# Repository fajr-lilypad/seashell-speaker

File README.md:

# Seashell Speaker!

A bluetooth speaker that automatically plays when tilted, encased in a seashell case!

I came up with this idea when I was thinking about how to expand my audio projects. This was created for hackclub's fallout program, and after first creating an mp3 player, I though the next step would be to make something that could use bluetooth, and then I took it to the next level by making it tilt activated! By coincidence, this is my second ocean-related project, lol. The design was inspired by the story we all know about hearing the ocean come from a shell, and partly inspired by the purple magic conch shell from spongebob, lol.

# Cad Screenshots

<table>
   <tr>
      <td>
   
</td>
      <td>
   
      </td>
   </tr>
</table>

<table>
  <tr>
    <td>
    
    </td>
    <td>
    
    </td>
    <td>
      
    </td>
  </tr>
</table>

Cad Notes:
- Okay, so CAD took a WHILE. Creating such an organic shape was difficult, so ended up relying on the revolve, sweep, and coil tools. Since there arent any tutorials online for creating this type of shell in Fusion either, I had to experiment with blender along with borrowing pieces of 3d models online. Once I had a shape i was happy with, I turned it into a case by splitting it in half, adding holes for magnets, and enclosure for the speaker standoffs for the pcb, and holes for the speaker wires.
- The case itself is pretty easy to use, and I'm happy with how it turned out. If I could go back and change anything, I'd definetly check before hand that my case and pcb were compatible. Orginally, I had planned to tuck my pcb away in the lip/opening of the shell. However, that would be pretty mush impossible without making a HUGE shell case, so I had to basically do a whole redesign of the pcb and case.

# PCB Screenshots

<table>
  <tr>
    <td>
    
    </td>
    <td>
    
    </td>
    <td>
      
    </td>
  </tr>
</table>

  PCB Notes:
   - For the PCB, I did have to go thorugh a few versions. I mostly focused on creating super compact board without hindering the esp32's antenna, which wasn't too bad. However, my first designs were too big too fit in the case, so I had to go back to the drawing board, where I decided to make a round pcb that would sit between the top and bottom halves of the shell.
   - This pcb includes a tilt sensor, charging module, switch, esp32, speaker output headers, and more (see bom)

# Schematic Screenshot

 # Zine !!

 # BOM

 | Item                 | Purpose                       | #        | Cost   | Supplier           | Link                                                                                                                                                                                                                                                                                                                                                                                                                                                                                                                                                                                                                                                                                                                                                                                                                                                                                                                                       |
|----------------------|-------------------------------|----------|--------|--------------------|--------------------------------------------------------------------------------------------------------------------------------------------------------------------------------------------------------------------------------------------------------------------------------------------------------------------------------------------------------------------------------------------------------------------------------------------------------------------------------------------------------------------------------------------------------------------------------------------------------------------------------------------------------------------------------------------------------------------------------------------------------------------------------------------------------------------------------------------------------------------------------------------------------------------------------------------|
| SW-520D              | Sensor                        | 1        | $1.13  | Aliexpress         | https://www.aliexpress.us/item/3256805875302445.html?spm=a2g0o.productlist.main.8.2a455a92Y7JwEt&aem_p4p_detail=202606091117086506985475300170000304694&algo_pvid=fe4f2528-e777-4706-bdc4-faf0cd102a94&algo_exp_id=fe4f2528-e777-4706-bdc4-faf0cd102a94-7&pdp_ext_f=%7B%22order%22%3A%22408%22%2C%22eval%22%3A%221%22%2C%22fromPage%22%3A%22search%22%7D&pdp_npi=6%40dis%21USD%211.13%210.99%21%21%217.60%216.63%21%40210311a017810290282231241ecb91%2112000035553543022%21sea%21US%210%21ABX%211%210%21n_tag%3A-29910%3Bd%3A3d07d826%3Bm03_new_user%3A-29895%3BpisId%3A5000000208023469&curPageLogUid=slAjiQRfgwbv&utparam-url=scene%3Asearch%7Cquery_from%3A%7Cx_object_id%3A1005006061617197%7C_p_origin_prod%3A&search_p4p_id=202606091117086506985475300170000304694_2                                                                                                                                                                |
| ESP32                | Microcontroller               | 1        | $3.13  | Aliexpress         | https://www.aliexpress.us/item/3256807714347051.html?spm=a2g0o.detail.pcDetailTopMoreOtherSeller.9.53d6LqkcLqkcL8&gps-id=pcDetailTopMoreOtherSeller&scm=1007.40050.354490.0&scm_id=1007.40050.354490.0&scm-url=1007.40050.354490.0&pvid=bbcfd485-a128-4b7e-bef7-387fe15564de&_t=gps-id%3ApcDetailTopMoreOtherSeller%2Cscm-url%3A1007.40050.354490.0%2Cpvid%3Abbcfd485-a128-4b7e-bef7-387fe15564de%2Ctpp_buckets%3A668%232846%238112%231997&pdp_ext_f=%7B%22order%22%3A%222175%22%2C%22eval%22%3A%221%22%2C%22sceneId%22%3A%2230050%22%2C%22fromPage%22%3A%22recommend%22%7D&pdp_npi=6%40dis%21USD%213.13%210.99%21%21%2121.08%216.62%21%40210311a017810284925912815ecb64%2112000057603495752%21rec%21US%21%21ABXZ%211%210%21n_tag%3A-29910%3Bd%3A3d07d826%3Bm03_new_user%3A-29895%3BpisId%3A5000000207262930&utparam-url=scene%3ApcDetailTopMoreOtherSeller%7Cquery_from%3A%7Cx_object_id%3A1005007900661803%7C_p_origin_prod%3A           |
| MAX98357A            | Amplifier                     | 1        | $1.78  | Aliexpress         | https://www.aliexpress.us/item/3256805196806369.html?gatewayAdapt=glo2usa4itemAdapt                                                                                                                                                                                                                                                                                                                                                                                                                                                                                                                                                                                                                                                                                                                                                                                                                                                        |
| Small Round Magnets  | Enclosure snaps               | 1        | $0.99  | Aliexpress         | https://www.aliexpress.us/item/3256810289404806.html?src=google&snps=y&src=google&albch=shopping&acnt=708-803-3821&isdl=y&slnk=&plac=&mtctp=&albbt=Google_7_shopping&aff_platform=google&aff_short_key=UneMJZVf&gclsrc=aw.ds&albagn=888888&ds_e_adid=&ds_e_matchtype=&ds_e_device=c&ds_e_network=x&ds_e_product_group_id=&ds_e_product_id=en3256810289404806&ds_e_product_merchant_id=5389452729&ds_e_product_country=US&ds_e_product_language=en&ds_e_product_channel=online&ds_e_product_store_id=&ds_url_v=2&albcp=20542171667&albag=&isSmbAutoCall=false&needSmbHouyi=false&gad_source=1&gad_campaignid=18545443176&gbraid=0AAAAAD6I-hEGa4vCjbQEz_fnmZhTeNZeX&gclid=CjwKCAjw6MPRBhBTEiwAd-7Mr0am_0D1CD1TBxs2bdRdSIcNnWCwfYTzIG0vOezmpeWGssT1TIOY-BoCo78QAvD_BwE&gatewayAdapt=glo2usa                                                                                                                                                   |
| 15mm speaker         | Speaker                       | 1        | $2.17  | Aliexpress         | https://www.aliexpress.us/item/3256809180147331.html?spm=a2g0o.detail.pcDetailBottomMoreOtherSeller.5.740cXUMeXUMeDJ&gps-id=pcDetailBottomMoreOtherSeller&scm=1007.40050.354490.0&scm_id=1007.40050.354490.0&scm-url=1007.40050.354490.0&pvid=86cf8570-e151-4a2b-b03f-eb252657f6d3&_t=gps-id%3ApcDetailBottomMoreOtherSeller%2Cscm-url%3A1007.40050.354490.0%2Cpvid%3A86cf8570-e151-4a2b-b03f-eb252657f6d3%2Ctpp_buckets%3A668%232846%238116%232002&pdp_ext_f=%7B%22order%22%3A%22121%22%2C%22eval%22%3A%221%22%2C%22sceneId%22%3A%2230050%22%2C%22fromPage%22%3A%22recommend%22%7D&pdp_npi=6%40dis%21USD%212.17%210.99%21%21%2114.55%216.62%21%402101e80f17815678571252704e2555%2112000048878174528%21rec%21US%21%21ABX%211%210%21n_tag%3A-29910%3Bd%3A3d07d826%3Bm03_new_user%3A-29895%3BpisId%3A5000000207262921&utparam-url=scene%3ApcDetailBottomMoreOtherSeller%7Cquery_from%3A%7Cx_object_id%3A1005009366462083%7C_p_origin_prod%3A |
| 3.7V Lithium Battery | Battery                       | 1        | $6.67  | Aliexpress         | https://www.aliexpress.us/item/3256803431098963.html?spm=a2g0o.productlist.main.5.104d2b945dhflO&algo_pvid=e2bc6e8e-31b3-4b37-b9c6-48889db5d69d&algo_exp_id=e2bc6e8e-31b3-4b37-b9c6-48889db5d69d-4&pdp_ext_f=%7B%22order%22%3A%22595%22%2C%22eval%22%3A%221%22%2C%22fromPage%22%3A%22search%22%7D&pdp_npi=6%40dis%21USD%2111.13%210.99%21%21%2111.13%210.99%21%402101dedf17810381549776117ed4ba%2112000031528245882%21sea%21US%210%21ABX%211%210%21n_tag%3A-29910%3Bd%3A3d07d826%3Bm03_new_user%3A-29895%3BpisId%3A5000000208023469&curPageLogUid=Xtp5n6hf7f32&utparam-url=scene%3Asearch%7Cquery_from%3A%7Cx_object_id%3A1005003617413715%7C_p_origin_prod%3A                                                                                                                                                                                                                                                                             |
| TP4056 Module        | Charging Module               | 1        | $0.82  | Aliexpress         | https://www.aliexpress.us/item/3256808777213556.html?spm=a2g0o.productlist.main.4.cab858c90o4EZr&aem_p4p_detail=2026060913085012854174373147450000384646&algo_pvid=a31457e4-4596-44d0-a1ee-68c03a0a6a34&algo_exp_id=a31457e4-4596-44d0-a1ee-68c03a0a6a34-3&pdp_ext_f=%7B%22order%22%3A%22258%22%2C%22eval%22%3A%221%22%2C%22fromPage%22%3A%22search%22%7D&pdp_npi=6%40dis%21USD%211.39%210.82%21%21%219.35%215.52%21%40210328df17810357308784740ebeee%2112000047390095230%21sea%21US%210%21ABX%211%210%21n_tag%3A-29910%3Bd%3A3d07d826%3Bm03_new_user%3A-29895&curPageLogUid=E6mZcshUD85X&utparam-url=scene%3Asearch%7Cquery_from%3A%7Cx_object_id%3A1005008963528308%7C_p_origin_prod%3A&search_p4p_id=2026060913085012854174373147450000384646_1                                                                                                                                                                                         |
| AP2112K              | Voltage Regulator             | 1        | $0.26  | Mouser             | https://www.mouser.com/ProductDetail/Diodes-Incorporated/AP2112K-33TRG1?qs=x6A8l6qLYDDPYHosCdzh%2FA%3D%3D&mgh=1&srsltid=AfmBOop7JC_vGrckd0OkIOnbCE54MlF8iCCVBWGQPHc_x9qankzlswPuAOs                                                                                                                                                                                                                                                                                                                                                                                                                                                                                                                                                                                                                                                                                                                                                        |
| 3Pin Slide Switch    | Off/On                        | 1        | $0.90  | Aliexpress         | https://www.aliexpress.us/item/2255801021214741.html?src=google&snps=y&src=google&albch=shopping&acnt=708-803-3821&isdl=y&slnk=&plac=&mtctp=&albbt=Google_7_shopping&aff_platform=google&aff_short_key=UneMJZVf&gclsrc=aw.ds&albagn=888888&ds_e_adid=&ds_e_matchtype=&ds_e_device=c&ds_e_network=x&ds_e_product_group_id=&ds_e_product_id=en2255801021214741&ds_e_product_merchant_id=5537905119&ds_e_product_country=US&ds_e_product_language=en&ds_e_product_channel=online&ds_e_product_store_id=&ds_url_v=2&albcp=20542171667&albag=&isSmbAutoCall=false&needSmbHouyi=false&gad_source=1&gad_campaignid=18545443176&gbraid=0AAAAAD6I-hHaLazO33f9UCgjrSDrxttdj&gclid=CjwKCAjw857RBhAgEiwAI-1yKGcUutsVjh7Hd-KUGzzBo5dwD5iBh8WG53Fq1rY3eMZGgkaT7h7BexoCyT8QAvD_BwE&gatewayAdapt=glo2usa                                                                                                                                                   |
| CH340C               | Serial Chip                   | 1        | $0.94  | Aliexpress         | https://www.aliexpress.us/item/3256809981619787.html?src=google&snps=y&src=google&albch=shopping&acnt=708-803-3821&isdl=y&slnk=&plac=&mtctp=&albbt=Google_7_shopping&aff_platform=google&aff_short_key=UneMJZVf&gclsrc=aw.ds&albagn=888888&ds_e_adid=&ds_e_matchtype=&ds_e_device=c&ds_e_network=x&ds_e_product_group_id=&ds_e_product_id=en3256809981619787&ds_e_product_merchant_id=5445838537&ds_e_product_country=US&ds_e_product_language=en&ds_e_product_channel=online&ds_e_product_store_id=&ds_url_v=2&albcp=20542171667&albag=&isSmbAutoCall=false&needSmbHouyi=false&gad_source=1&gad_campaignid=18545443176&gbraid=0AAAAAD6I-hHaLazO33f9UCgjrSDrxttdj&gclid=CjwKCAjw857RBhAgEiwAI-1yKF3C_t6BfukCoI2MIAqUoIj5av7RzRFhyHopu9oc85gfqWgypX8g6BoC844QAvD_BwE&gatewayAdapt=glo2usa                                                                                                                                                   |
| JST 2 Pin Connector  | battery input, speaker output | 2        | $1.97  | Aliexpress         | https://www.aliexpress.us/item/3256808498055527.html?src=google&snps=y&src=google&albch=shopping&acnt=708-803-3821&isdl=y&slnk=&plac=&mtctp=&albbt=Google_7_shopping&aff_platform=google&aff_short_key=UneMJZVf&gclsrc=aw.ds&albagn=888888&ds_e_adid=&ds_e_matchtype=&ds_e_device=c&ds_e_network=x&ds_e_product_group_id=&ds_e_product_id=en3256808498055527&ds_e_product_merchant_id=419595364&ds_e_product_country=US&ds_e_product_language=en&ds_e_product_channel=online&ds_e_product_store_id=&ds_url_v=2&albcp=20542171667&albag=&isSmbAutoCall=false&needSmbHouyi=false&gad_source=1&gad_campaignid=18545443176&gbraid=0AAAAAD6I-hHaLazO33f9UCgjrSDrxttdj&gclid=CjwKCAjw857RBhAgEiwAI-1yKIfph2TVNGbNjJQvX5Zj27htVAhFcW1687lGfd6tPNRwOX1nvVZPAxoCC8cQAvD_BwE&gatewayAdapt=glo2usa                                                                                                                                                    |
| USB C Receptacle     | Data Input                    | 1        | $2.02  | Aliexpress         | https://www.aliexpress.us/item/3256809263109556.html?spm=a2g0o.productlist.main.4.3bcc19968KRtiX&aem_p4p_detail=202606091354198020055955219420000447194&algo_pvid=e7187bb7-d172-4502-9b1f-e094f1977ab8&algo_exp_id=e7187bb7-d172-4502-9b1f-e094f1977ab8-3&pdp_ext_f=%7B%22order%22%3A%22146%22%2C%22eval%22%3A%221%22%2C%22fromPage%22%3A%22search%22%7D&pdp_npi=6%40dis%21USD%212.02%210.99%21%21%2113.61%216.65%21%402101e81117810384594691903e21a7%2112000049137415204%21sea%21US%210%21ABX%211%210%21n_tag%3A-29910%3Bd%3A3d07d826%3Bm03_new_user%3A-29895%3BpisId%3A5000000208023469&curPageLogUid=usEKz8Sk1Wvi&utparam-url=scene%3Asearch%7Cquery_from%3A%7Cx_object_id%3A1005009449424308%7C_p_origin_prod%3A&search_p4p_id=202606091354198020055955219420000447194_1                                                                                                                                                               |
| WS2812B              | LED                           | 2        | $0.20  | Ebee               | https://www.ebee.com/product-detail/worldsemi-ws2812b-v5-w_617514.html?gad_source=1&gad_campaignid=22818797232&gbraid=0AAAABAZS-mZ97kvrRYudRCfHYeKSVd23P&gclid=Cj0KCQjw0JnRBhDJARIsALobnXbpNoaM8TbHHZTgba2UspdfY-oN8lfFjU0dsez_f3c1VV_Ib0_YNKMaAifpEALw_wcB                                                                                                                                                                                                                                                                                                                                                                                                                                                                                                                                                                                                                                                                                |
| 74ACHCT125           | Quad Level Shifter            | 1        | $1.50  | Adafruit           | https://www.adafruit.com/product/1787?gad_source=4&gad_campaignid=21079227318&gbraid=0AAAAADx9JvQwz_dcNQ8xPVA_S3ZzMPYbt&gclid=CjwKCAjwuanRBhBSEiwAY5y6V59-y8qPmSYGvPf51QWwdpDNnrvIvFix85_3gRVjNSMnHIcPbMs9DxoCzLIQAvD_BwE                                                                                                                                                                                                                                                                                                                                                                                                                                                                                                                                                                                                                                                                                                                  |
| 10uF C               | Capacitor                     | 3        | $0.40  | Digikey            | https://www.digikey.com/en/products/detail/kyocera-avx/REA0511100M025K/20096372?gclsrc=aw.ds&gad_source=1&gad_campaignid=20682862038&gbraid=0AAAAADrbLlg0zCO2nMN9oOFXGoIwVJrS6&gclid=Cj0KCQjw0JnRBhDJARIsALobnXYPCey9XhELbus8p4oBeSzUM1fkyno59aOY1zw6VVWGtJGkAox3TrsaAmw4EALw_wcB                                                                                                                                                                                                                                                                                                                                                                                                                                                                                                                                                                                                                                                          |
| 0.1uF C              | Capacitor                     | 5        | $0.32  | Sparkfun           | https://www.sparkfun.com/capacitor-ceramic-0-1uf.html                                                                                                                                                                                                                                                                                                                                                                                                                                                                                                                                                                                                                                                                                                                                                                                                                                                                                      |
| 5.1K R               | Resistor                      | 2        | $0.08  | Electronix Express | https://www.elexp.com/products/130155-1kres-1-watt-5-5-1-k-ohm?variant=42620564504804&country=US&currency=USD&utm_medium=product_sync&utm_source=google&utm_content=sag_organic&utm_campaign=sag_organic&srsltid=AfmBOoqKgWPBG0shD9zpuYg7Psf4nfMv1r5sR8Nr0Ir3SL3qnrRQrXJ_9UA                                                                                                                                                                                                                                                                                                                                                                                                                                                                                                                                                                                                                                                               |
| 330 R                | Resistor                      | 1        | $0.15  | Newark             | https://www.newark.com/multicomp-pro/mccfr01sj0331a10/carbon-film-resistor-330-ohm-1w/dp/59K8549?CMP=KNC-BUSA-GEN-Shopping-ALL&mckv=s_dc|pcrid||plid||kword||match|e|slid||product|59K8549|pgrid|1231453304461926|ptaid|pla-4580565455222458|&msclkid=0d6d44d2aa3b1af1a3812efec2f401f3                                                                                                                                                                                                                                                                                                                                                                                                                                                                                                                                                                                                                                                     |
| 10K R                | Resistor                      | 3        | $0.19  | Newark             | https://www.newark.com/multicomp-pro/mf12-10k/res-10k-125mw-axial-metal-film/dp/38K5401?CMP=KNC-GUSA-PMAX-SHOPPING-ONBOARD-COMP-NEW&gad_source=1&gad_campaignid=22957739450&gbraid=0AAAAAD5U_g2ATgQ2NG2je9ALfN8sx9jn8&gclid=Cj0KCQjw0JnRBhDJARIsALobnXaCMZy09SS6FHr-OHNYzwHpClJ-m80lx3xV-T8LpQe5MepvkQgdvkEaAqznEALw_wcB                                                                                                                                                                                                                                                                                                                                                                                                                                                                                                                                                                                                                   |
| 100K R               | Resistor                      | 1        | $0.24  | Newark             | https://www.newark.com/ohmite/mox70031003bye/resistor-metal-film-100k-0-25w/dp/49AJ2825?CMP=KNC-BUSA-GEN-Shopping-ALL&mckv=s_dc|pcrid||plid||kword||match|e|slid||product|49AJ2825|pgrid|1231453304461926|ptaid|pla-4580565455222458|&msclkid=8346f4e1e0f2133c086d9ecd89969e59                                                                                                                                                                                                                                                                                                                                                                                                                                                                                                                                                                                                                                                             |
| S8050                | Transistor                    | 1        | $0.84  | Aliexpress         | https://www.aliexpress.us/item/3256808228534673.html?src=google&gatewayAdapt=glo2usa                                                                                                                                                                                                                                                                                                                                                                                                                                                                                                                                                                                                                                                                                                                                                                                                                                                       |
| BC847                | Transistor                    | 1        | $0.19  | Mouser             | https://www.mouser.com/ProductDetail/Nexperia/BC847235?qs=me8TqzrmIYXhyQltfPL4ag%3D%3D&mgh=1&utm_id=23744632239&utm_source=google&utm_medium=cpc&utm_marketing_tactic=amercorp&gad_source=4&gad_campaignid=23749957841&gbraid=0AAAAADn_wf3kKdcTpYOHBjeY97hvuN6Uc&gclid=Cj0KCQjw3K7RBhDJARIsAKRtP5R-iiAIbhYltHezTJVjofMJQRa0hawPOUwdilNXEpeREtUudNb10pkaAt5FEALw_wcB                                                                                                                                                                                                                                                                                                                                                                                                                                                                                                                                                                        |
| PCB Order            | PCB                           | 1        | $2.10  | JLCPCB             |                                                                                                                                                                                                                                                                                                                                                                                                                                                                                                                                                                                                                                                                                                                                                                                                                                                                                                                                            |
|                      |                               | Subtotal | $28.99 |                    |                                                                                                                                                                                                                                                                                                                                                                                                                                                                                                                                                                                                                                                                                                                                                                                                                                                                                                                                            |

## Firmware

Unlike my previous audio projects, instead of using a micro sd card storing songs played by a df player, I used bluetooth connection via an esp32 and a BluetoothA2DPSink library I found from user pschatzmann. The code is fairly simple, and checks the tilt sensor in the background periodically, intercepting when a tilt is detected to pause/play audio.

## Build Guide
1. 3D print Case, ensure that standoffs and holes are secure and remove all supports.
2. Collect all electronic parts and perform breadboard testing before soldering onto custom pcb
3. Flash fimrware with new pcb, connect to bluetooth so you see "Bluetooth Speaker Audio Ready to Pair!" message printed.
4. Test out tilt puasing/playing audio
5. Mount fully charged pcb onto built in standoffs in top of case.
6. Place speaker in enclosure, thread wires through holes and plug into headers in pcb.
7. Place magnets in small holes in shell case, snap case shut.

## Notes and Acknowledgements
- Thank you to *hackclub* and the *fallout* team for this oppurtunity and for making this project possible!

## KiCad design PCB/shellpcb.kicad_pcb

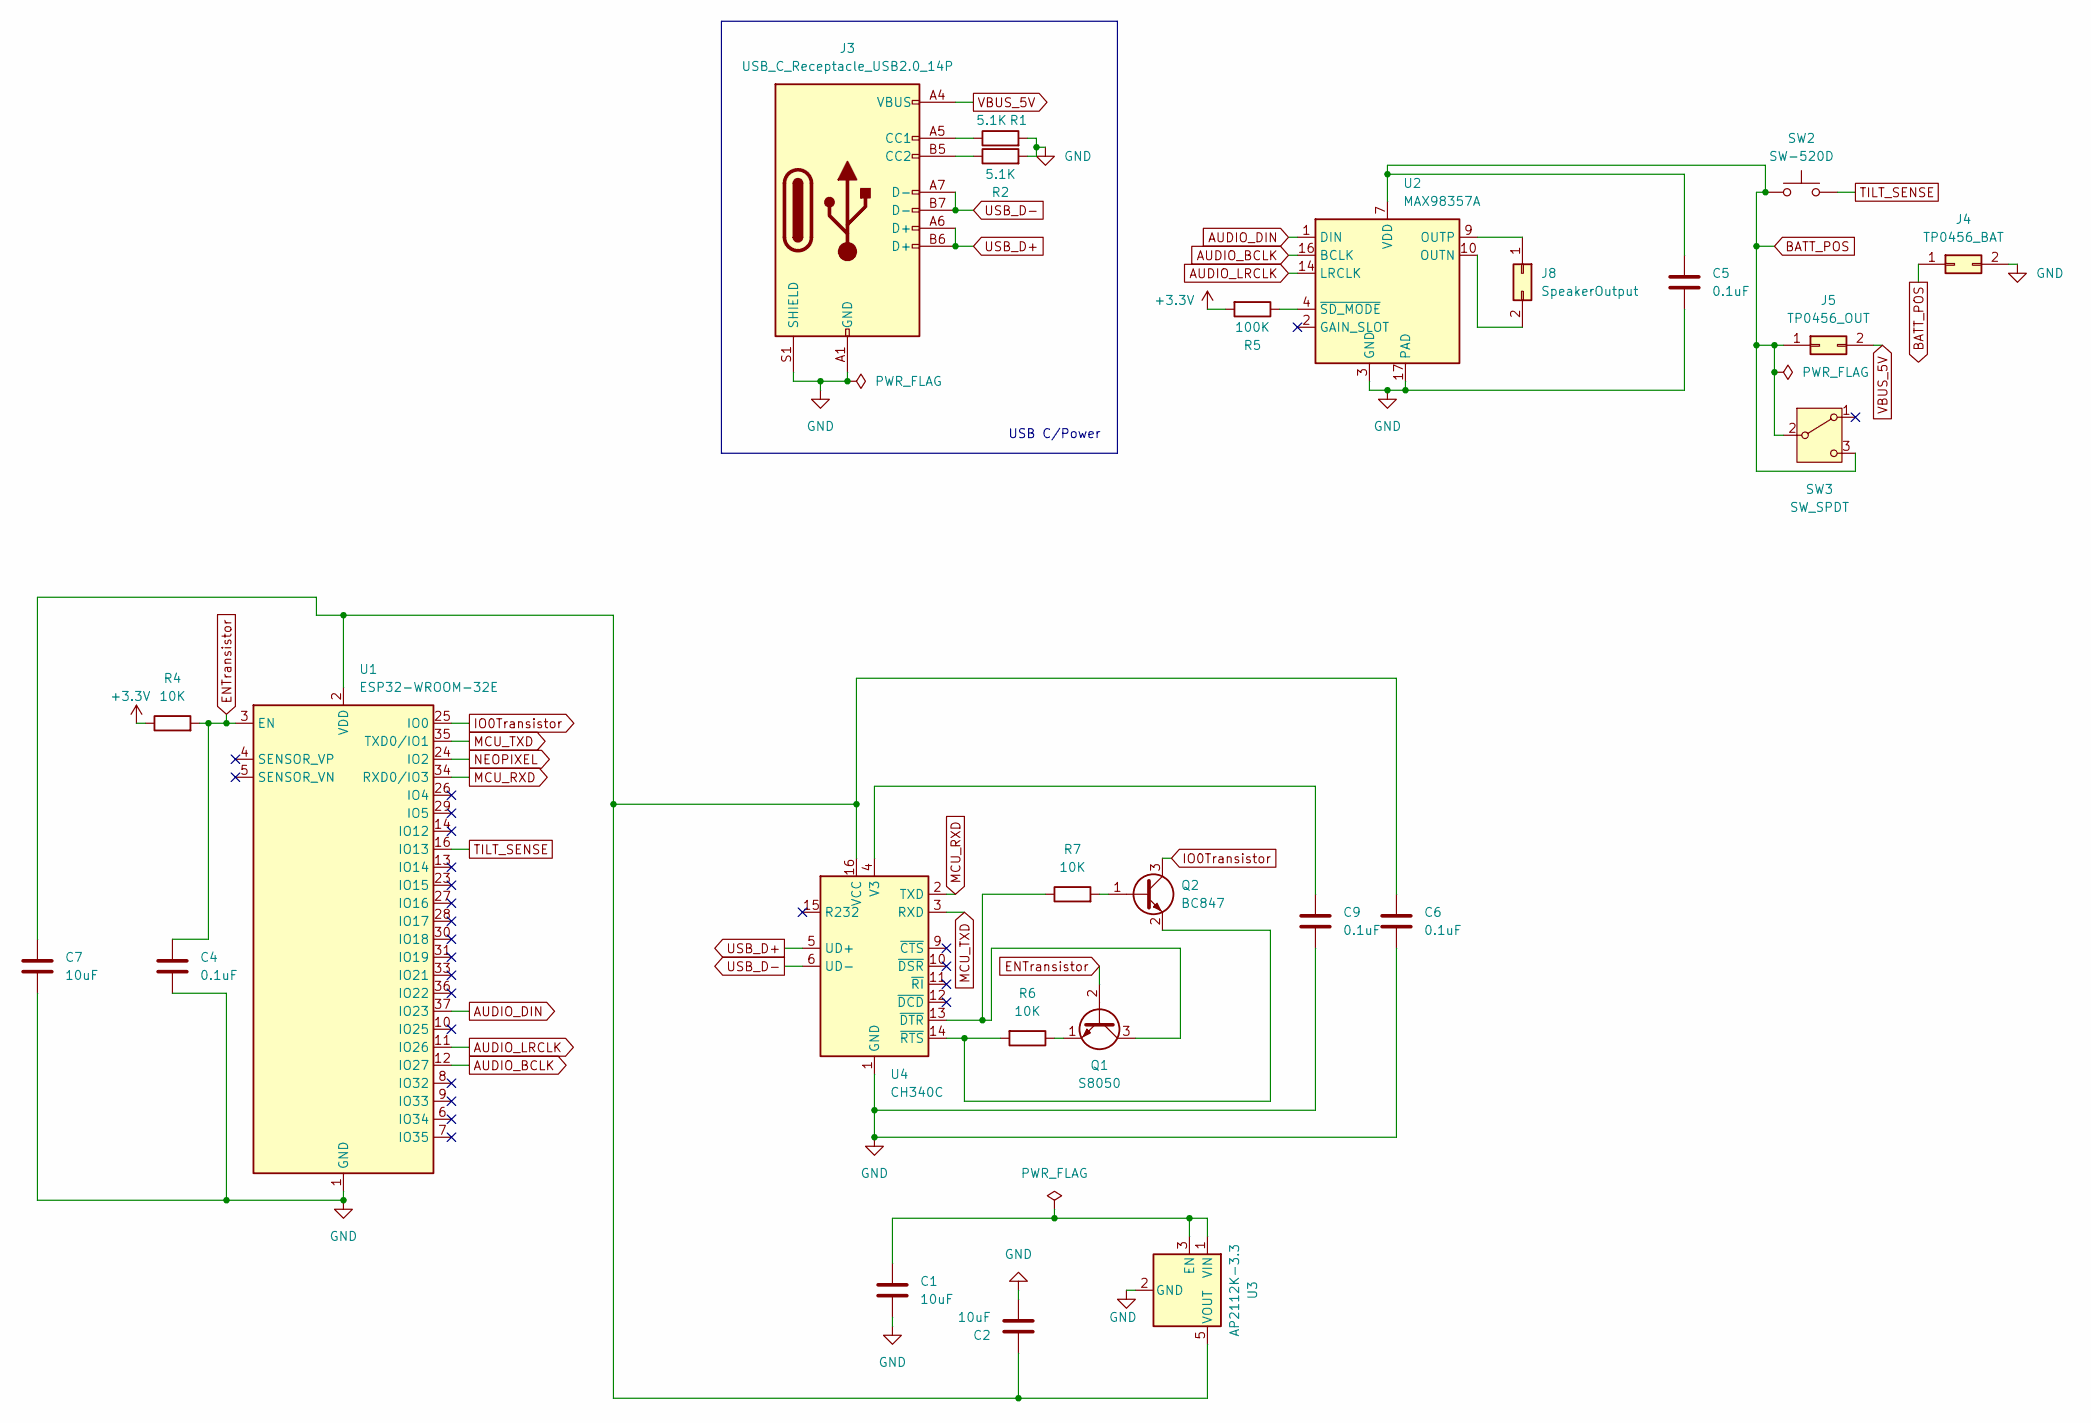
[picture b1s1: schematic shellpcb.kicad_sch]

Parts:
C1, C2, C7: 10uF; C_0603_1608Metric
C4, C5, C6, C9: 0.1uF; C_0402_1005Metric
J3: USB_C_Receptacle_USB2.0_14P; USB_C_Receptacle_HRO_TYPE-C-31-M-12
J4: TP0456_BAT; Batside
J5: TP0456_OUT; Outside
J8: SpeakerOutput; PinHeader_1x03_P2.54mm_Vertical
Q1: S8050; TO-92_Inline
Q2: BC847; SOT-23
R1, R2: 5.1K; R_0402_1005Metric
R4, R6, R7: 10K; R_0402_1005Metric
R5: 100K; R_0402_1005Metric
SW2: SW-520D; PinHeader_1x02_P2.54mm_Vertical
SW3: SW_SPDT; SW_Slide_SPDT_Straight_CK_OS102011MS2Q
U1: ESP32-WROOM-32E; ESP32-WROOM-32D
U2: MAX98357A; TQFN-16-1EP_3x3mm_P0.5mm_EP1.6x1.6mm
U3: AP2112K-3.3; SOT-23-5
U4: CH340C; SOIC-16_3.9x9.9mm_P1.27mm

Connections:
+3.3V: R4.1, R5.2
AUDIO_BCLK: U1.12 (IO27), U2.16 (BCLK)
AUDIO_DIN: U1.37 (IO23), U2.1 (DIN)
AUDIO_LRCLK: U1.11 (IO26), U2.14 (LRCLK)
BATT_POS: C5.1, J4.1, J5.1, SW2.1, SW3.2 (B), SW3.3 (C), U2.7 (VDD), U2.8 (VDD)
ENTransistor: C4.1, Q1.2 (B), R4.2, U1.3 (EN)
GND: C1.2, C2.1, C4.2, C5.2, C6.2, C7.2, C9.2, J3.A1 (GND), J3.A12 (GND), J3.B1 (GND), J3.B12 (GND), J3.S1 (SHIELD), J4.2, R1.2, R2.2, U1.1 (GND), U1.15 (GND), U1.38 (GND), U1.39 (GND), U2.3 (GND), U2.11 (GND), U2.15 (GND), U2.17 (PAD), U3.2 (GND), U4.1 (GND)
IO0Transistor: Q2.3 (C), U1.25 (IO0)
MCU_RXD: U1.34 (RXD0/IO3), U4.2 (TXD)
MCU_TXD: U1.35 (TXD0/IO1), U4.3 (RXD)
NEOPIXEL: U1.24 (IO2)
unnamed: J3.A5 (CC1), R1.1
unnamed: J3.B5 (CC2), R2.1
unnamed: J8.1, U2.9 (OUTP)
unnamed: J8.2, U2.10 (OUTN)
unnamed: Q1.3 (C), R7.1, U4.13 (~DTR)
unnamed: Q1.1 (E), R6.1
unnamed: Q2.1 (B), R7.2
unnamed: Q2.2 (E), R6.2, U4.14 (~RTS)
unnamed: C2.2, C6.1, C7.1, U1.2 (VDD), U3.5 (VOUT), U4.16 (VCC)
unnamed: R5.1, U2.4 (~SD_MODE)
unnamed: C1.1, U3.1 (VIN), U3.3 (EN)
unnamed: C9.1, U4.4 (V3)
TILT_SENSE: SW2.2, U1.16 (IO13)
USB_D+: J3.A6 (D+), J3.B6 (D+), U4.5 (UD+)
USB_D-: J3.A7 (D-), J3.B7 (D-), U4.6 (UD-)
VBUS_5V: J3.A4 (VBUS), J3.A9 (VBUS), J3.B4 (VBUS), J3.B9 (VBUS), J5.2

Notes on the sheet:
USB C/Power

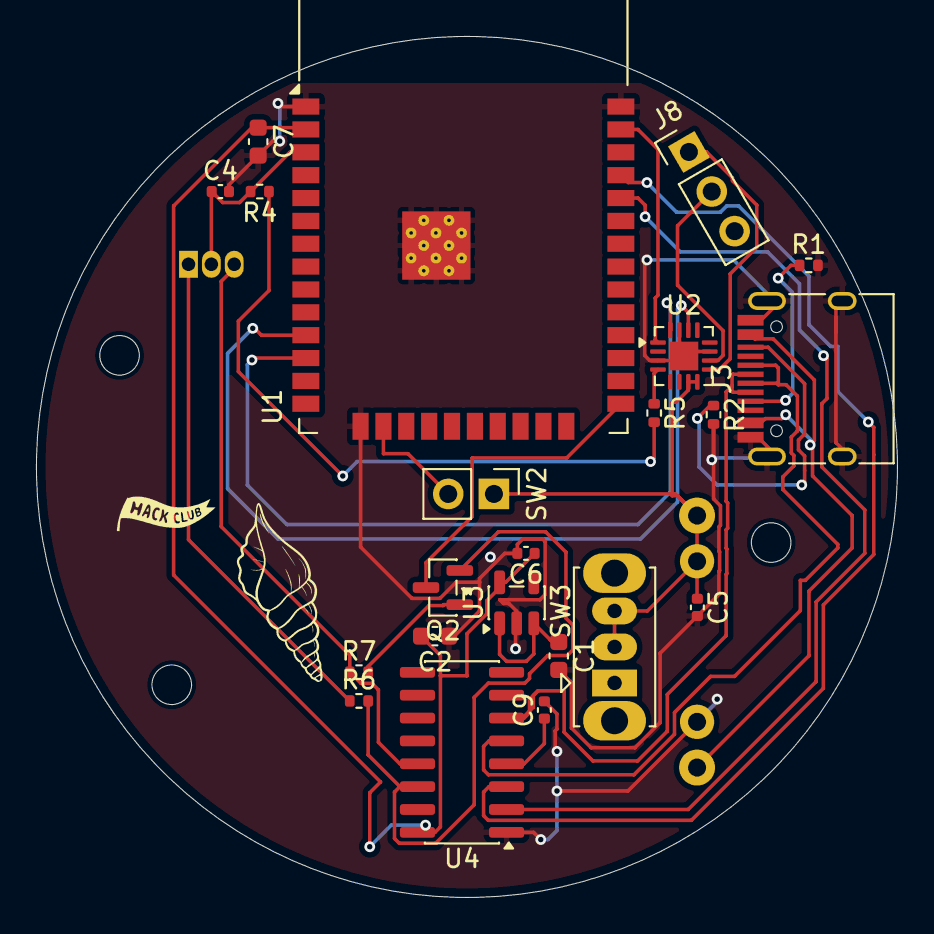
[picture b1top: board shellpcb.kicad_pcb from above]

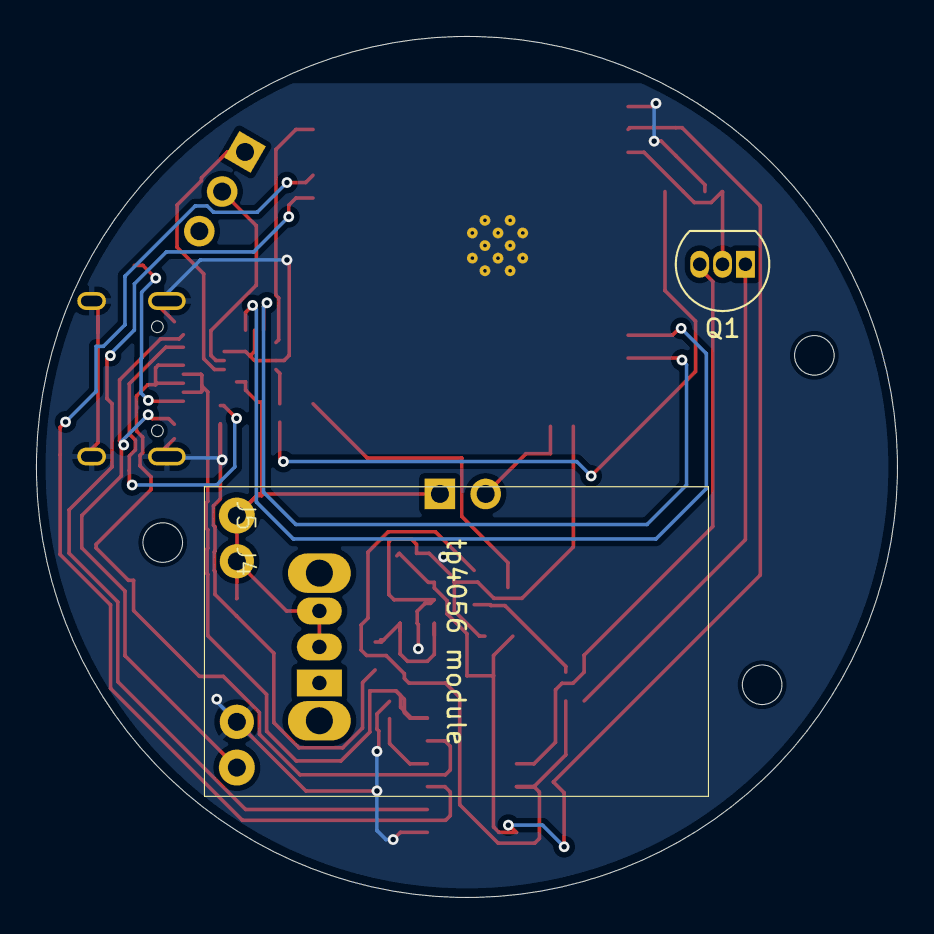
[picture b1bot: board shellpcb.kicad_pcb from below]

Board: 2 copper layers, 47.8 x 47.8 mm, 25 parts (3 on the bottom side), 26 nets.

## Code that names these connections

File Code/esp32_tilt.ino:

_#include "ESP_I2S.h" // Modern ESP32 Core v3+ Audio Driver

// Define your exact schematic pins
#define TILT_SWITCH_PIN   12  // SW2 connected to IO12
#define I2S_BCLK          26  // AUDIO_BCLK on IO26
#define I2S_LRCK          27  // AUDIO_LRCLK on IO27
#define I2S_DOUT          25  // AUDIO_DIN on IO25

// Create the modern audio output object
I2SClass i2s;

void setup() {
  Serial.begin(115200);
  
  //Configure the Tilt Switch pin with internal pull-up resistor
  pinMode(TILT_SWITCH_PIN, INPUT_PULLUP);

  // Initialize Modern I2S Driver pins
  i2s.setPins(I2S_BCLK, I2S_LRCK, I2S_DOUT, -1, -1); // (BCLK, WS/LRCK, DOUT, DIN, MCLK)
  
  // Start I2S
  // Mode, Sample Rate, Bits per Sample, and Channel Slot Mode
  if (!i2s.begin(I2S_MODE_STD, 44100, I2S_DATA_BIT_WIDTH_16BIT, I2S_SLOT_MODE_STEREO)) {
    Serial.println("Failed to initialize I2S audio module!");
    while (1); // Halt if audio fails
  }

  Serial.println("Sound-Only Hardware Initialized Successfully!");
}

void loop() {
  // Reading status of tilt sensor
  int switchState = digitalRead(TILT_SWITCH_PIN);

  if (switchState == LOW) {
    Serial.println("Shell Status: Level / Upright");
  } else {
    Serial.println("Shell Status: Tilted / Moved!");
  }

  delay(200); //delay
}

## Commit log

2026-06-12 Rename conchshell.zip to PCB/conchshell.zip
2026-06-16 Rename pcb (no components).step to CAD/PCB Files/pcb (no components).step
2026-06-16 Rename CAD/PCB Files/ESP32-C3-DEVKITM-1--3DModel-STEP-56544.STEP to CAD/PCB Files/Electronics/ESP32-C3-DEVKITM-1--3DModel-STEP-56544.STEP
2026-06-16 Rename shellpcbv2.zip to PCB/shellpcbv2.zip
2026-06-16 Rename CAD/Shell Case Top.step to CAD/Case/Shell Case Top.step
2026-06-16 Rename CAD/Shell Case bottom.step to CAD/Case/Shell Case bottom.step
2026-06-17 Rename Full Assembly.f3z to CAD/Full Assembly.f3z
2026-06-17 Rename esp32_tilt.ino to Code/esp32_tilt.ino
2026-06-17 Rename Screenshot 2026-06-17 150042.png to Schematic/Screenshot 2026-06-17 150042.png
2026-06-17 Rename Screenshot 2026-06-17 150042.png to Schematic.png
